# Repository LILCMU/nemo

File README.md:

# nemo
Water tank measurement and interface board

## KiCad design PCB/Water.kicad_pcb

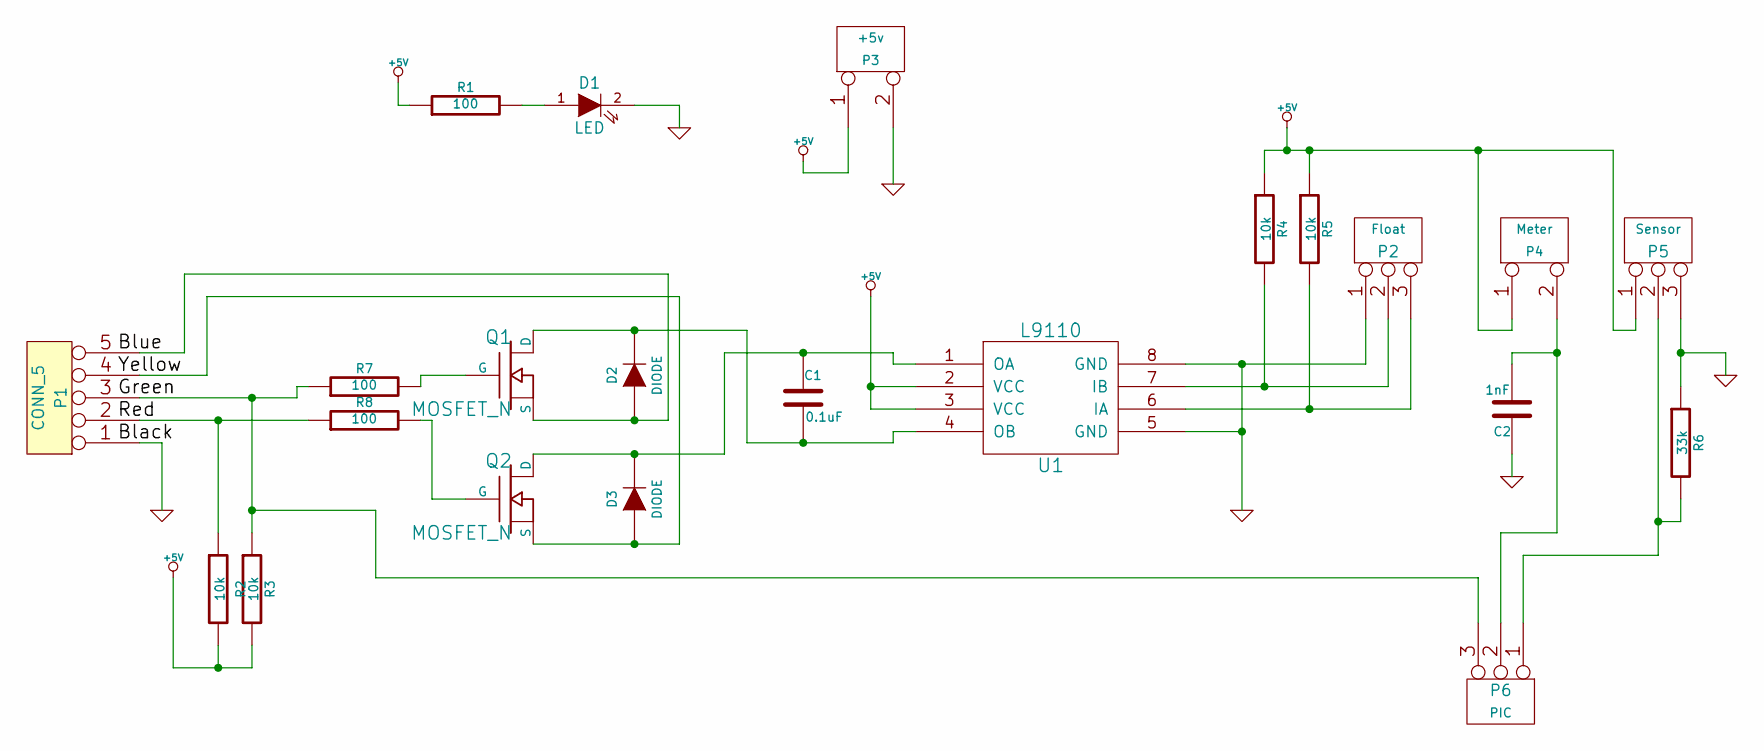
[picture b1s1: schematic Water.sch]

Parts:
C1: 0.1uF
C2: 1nF
D1: LED
D2, D3: DIODE
P1: CONN_5
P2: Float
P3: +5v
P4: Meter
P5: Sensor
P6: PIC
Q1, Q2: MOSFET_N
R1, R7, R8: 100
R2, R3, R4, R5: 10k
R6: 33k
U1: L9110

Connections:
+5V: P3.1, P4.1, P5.1, R1.1, R2.2, R3.2, R4.1, R5.1, U1.2 (VCC), U1.3 (VCC)
GND: C2.1, D1.2 (K), P1.1, P2.1, P3.2 (PM), P5.3, R6.1, U1.5 (GND), U1.8 (GND)
unnamed: P5.2 (PM), P6.1, R6.2
unnamed: P1.3, P6.3, R3.1, R7.1
unnamed: C2.2, P4.2 (PM), P6.2 (PM)
unnamed: Q1.G, R7.2
unnamed: P1.2, R2.1, R8.1
unnamed: Q2.G, R8.2
unnamed: D2.1 (A), P1.5, Q1.S
unnamed: C1.2, D2.2 (K), Q1.D, U1.4 (OB)
unnamed: D3.1 (A), P1.4, Q2.S
unnamed: P2.2 (PM), R4.2, U1.7 (IB)
unnamed: P2.3, R5.2, U1.6 (IA)
unnamed: D1.1 (A), R1.2
unnamed: C1.1, D3.2 (K), Q2.D, U1.1 (OA)

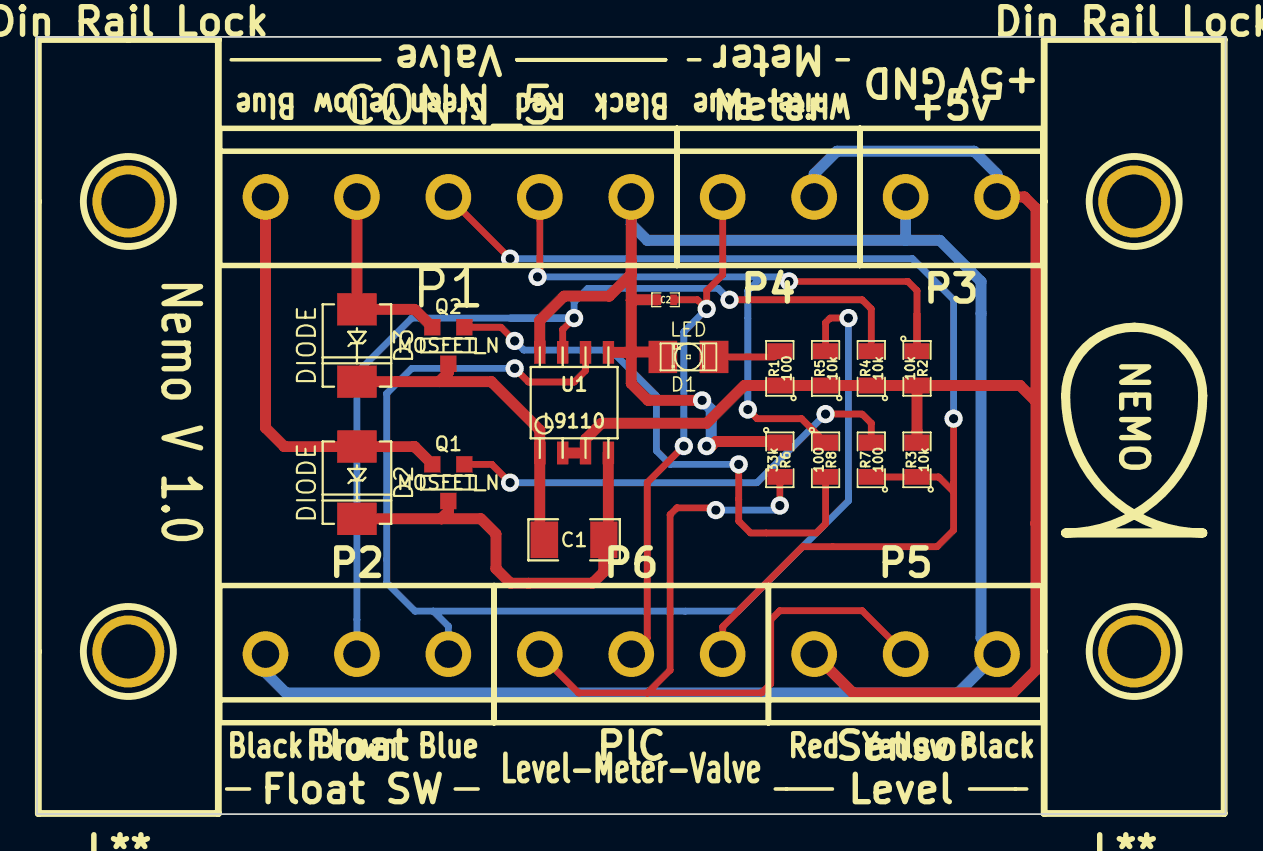
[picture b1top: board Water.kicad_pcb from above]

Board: 2 copper layers, 66.0 x 43.2 mm, 24 parts (0 on the bottom side), 15 nets.

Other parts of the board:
Din Rail Lock: L**; Din_Rail_Lock
Din Rail Lock#2: L**; Din_Rail_Lock

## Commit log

2016-07-25 Add code
2016-07-25 Add PCB files
